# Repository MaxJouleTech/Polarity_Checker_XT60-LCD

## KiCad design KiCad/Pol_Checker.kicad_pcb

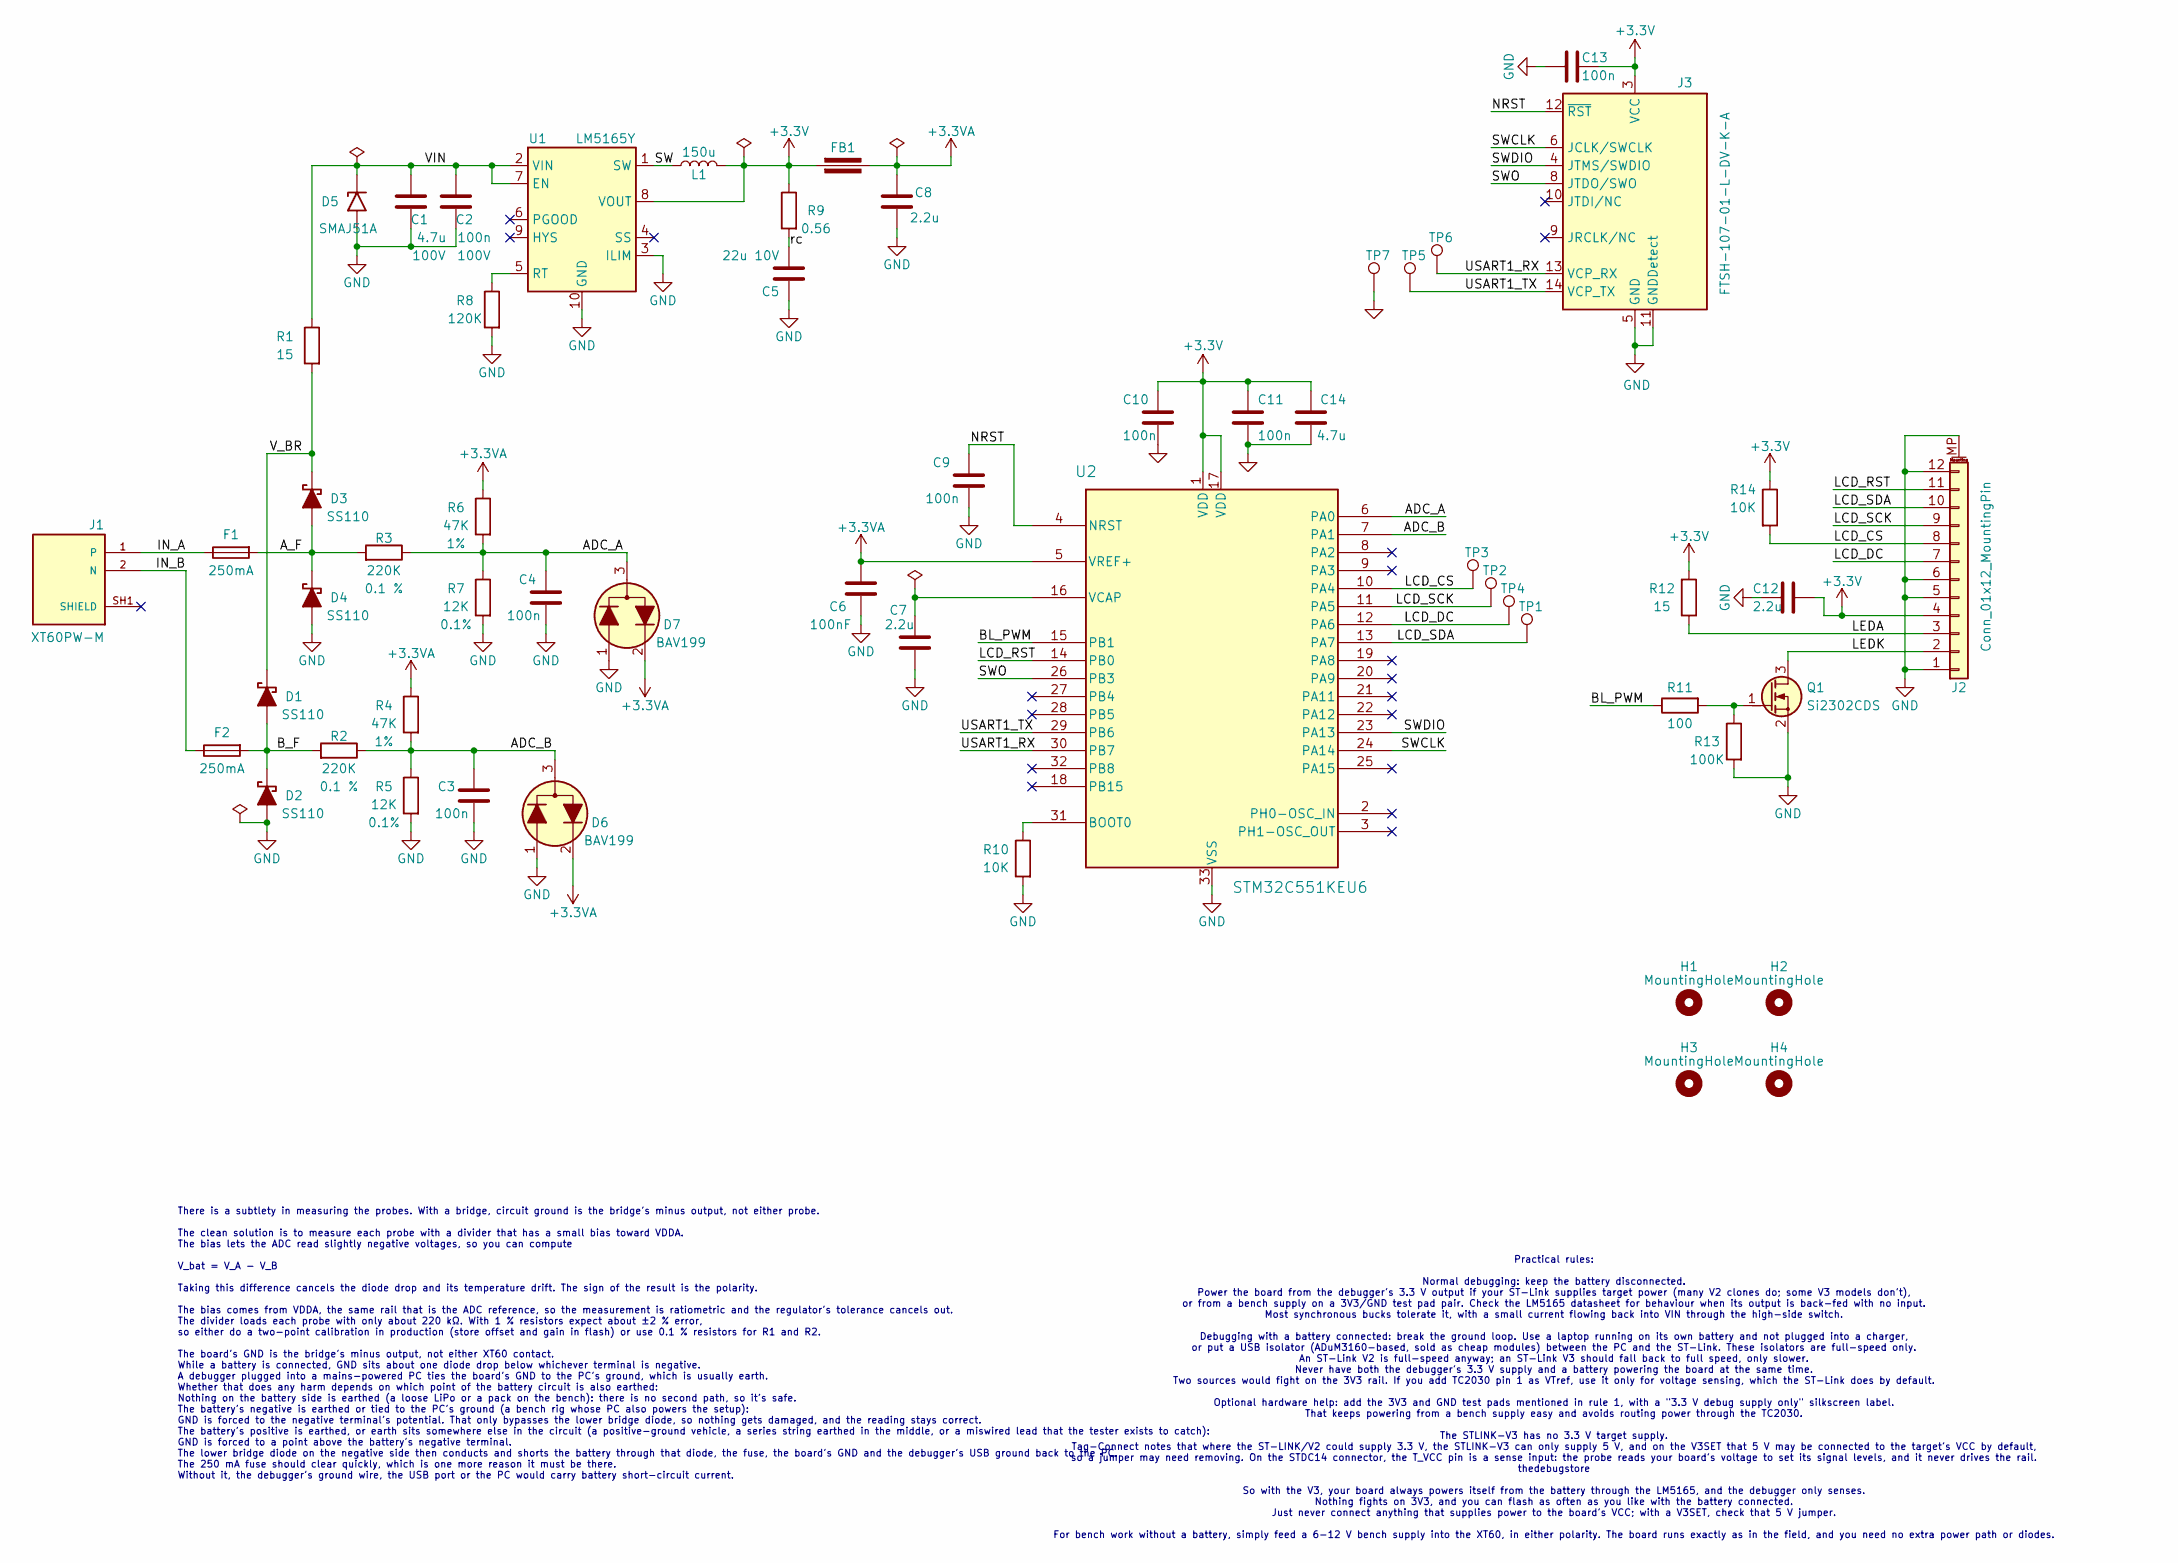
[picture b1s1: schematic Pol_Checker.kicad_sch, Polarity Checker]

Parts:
C1: 4.7u; C_1206_3216Metric; Tolerance 100V; MPN GRJ31CZ72A475ME01L
C2: 100n; C_0805_2012Metric; Tolerance 100V; MPN CL21B104KCFWPJF
C3, C4, C9, C10, C11, C13: 100n; C_0603_1608Metric; Tolerance 50V; MPN CL10B104KB8WPNC
C5: 22u 10V; C_1206_3216Metric; Tolerance 10V; MPN CL31B226KPHNNNE
C6: 100nF; C_0805_2012Metric; Tolerance 50V; MPN CL21B104KBCNFNC
C7, C8, C12: 2.2u; C_0805_2012Metric; Tolerance 25V; MPN CL21B225KAFNNNE
C14: 4.7u; C_0805_2012Metric; Tolerance 16V; MPN CL21A475KOFNNNG
D1, D2, D3, D4: SS110; D_SMA; MPN SS110LS
D5: SMAJ51A; D_SMA; MPN SMAJ51A-13-F
D6, D7: BAV199; SOT-23; MPN BAV199LT1G
F1, F2: 250mA; Fuse_1206_3216Metric; MPN 0466.250NR
FB1: Ferrite_Bead; L_0805_2012Metric; MPN BLM21PG221SN1D
H1, H2, H3, H4: MountingHole; MountingHole_2.2mm_M2
J1: XT60PW-M; AMASS_XT60PW-M; PARTREV 1.2
J2: Conn_01x12_MountingPin; Hirose_FH12-12S-0.5SH_1x12-1MP_P0.50mm_Horizontal; MPN FH12-12S-0.5SH(55)
J3: FTSH-107-01-L-DV-K-A; PinHeader_2x07_P1.27mm_Vertical_SMD; MPN FTSH-107-01-L-DV-K-A
L1: 150u; L_Coilcraft_LPS5030; MPN LPS5030-154MR
Q1: Si2302CDS; SOT-23; MPN SI2302CDS-T1-E3
R1: 15; R_1206_3216Metric; Tolerance 1%; MPN RC0603FR-0715RL
R2, R3: 220K; R_0805_2012Metric; Tolerance 0.1 %; MPN RP0603BRD07220KL
R4, R6: 47K; R_0603_1608Metric; Tolerance 1%; MPN RC0603FR-0747KL
R5, R7: 12K; R_0603_1608Metric; Tolerance 0.1%; MPN RT0603BRE0712KL
R8: 120K; R_0603_1608Metric; Tolerance 1%; MPN RC0603FR-10120KL
R9: 0.56; R_0603_1608Metric; Tolerance 1%; MPN RL0603FR-070R56L
R10, R14: 10K; R_0603_1608Metric; Tolerance 1%; MPN RC0603FR-0710KL
R11: 100; R_0603_1608Metric; Tolerance 1%; MPN RC0603FR-07100RL
R12: 15; R_0603_1608Metric; Tolerance 1%; MPN RC0603FR-0715RL
R13: 100K; R_0603_1608Metric; Tolerance 1%; MPN RC0603FR-07100KL
TP1, TP2, TP3, TP4, TP5, TP6: TestPoint; TestPoint_Pad_D1.5mm
TP7: TestPoint; TestPoint_Pad_2.0x2.0mm
U1: LM5165Y; Texas_S-PVSON-N10_ThermalVias; MPN LM5165YDRCR
U2: STM32C551KEU6; QFN-32-1EP_5x5mm_P0.5mm_EP3.1x3.1mm_ThermalVias; MPN STM32C551KEU6

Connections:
+3.3V: C10.2, C11.2, C12.1, C13.1, C14.1, FB1.1, J2.4, J3.3 (VCC), L1.2, R9.1, R12.2, R14.1, U1.8 (VOUT), U2.1 (VDD), U2.17 (VDD)
+3.3VA: C6.1, C8.1, D6.2 (K), D7.2 (K), FB1.2, R4.1, R6.1, U2.5 (VREF+)
/ADC_A: C4.1, D7.3 (C), R3.1, R6.2, R7.1, U2.6 (PA0)
/ADC_B: C3.1, D6.3 (C), R2.1, R4.2, R5.1, U2.7 (PA1)
/A_F: D3.2 (A), D4.1 (K), F1.2, R3.2
/BL_PWM: R11.1, U2.15 (PB1)
/B_F: D1.2 (A), D2.1 (K), F2.2, R2.2
/IN_A: F1.1, J1.1
/IN_B: F2.1, J1.2 (N)
/LCD_CS: J2.8, R14.2, TP3.1 (1_1), U2.10 (PA4)
/LCD_DC: J2.7, TP4.1 (1_1), U2.12 (PA6)
/LCD_RST: J2.11, U2.14 (PB0)
/LCD_SCK: J2.9, TP2.1 (1_1), U2.11 (PA5)
/LCD_SDA: J2.10, TP1.1 (1_1), U2.13 (PA7)
/LEDA: J2.3, R12.1
/LEDK: J2.2, Q1.3 (D)
/NRST: C9.1, J3.12 (~RST), U2.4 (NRST)
/SW: L1.1, U1.1 (SW)
/SWCLK: J3.6 (JCLK/SWCLK), U2.24 (PA14)
/SWDIO: J3.4 (JTMS/SWDIO), U2.23 (PA13)
/SWO: J3.8 (JTDO/SWO), U2.26 (PB3)
/USART1_RX: J3.13 (VCP_RX), TP6.1 (1_1), U2.30 (PB7)
/USART1_TX: J3.14 (VCP_TX), TP5.1 (1_1), U2.29 (PB6)
/VIN: C1.1, C2.1, D5.1 (A1), R1.1, U1.2 (VIN), U1.7 (EN)
/V_BR: D1.1 (K), D3.1 (K), R1.2
/rc: C5.1, R9.2
GND: C1.2, C2.2, C3.2, C4.2, C5.2, C6.2, C7.2, C8.2, C9.2, C10.1, C11.1, C12.2, C13.2, C14.2, D2.2 (A), D4.2 (A), D5.2 (A2), D6.1 (A), D7.1 (A), J2.1, J2.5, J2.6, J2.12, J2.MP (MountPin), J3.5 (GND), J3.7 (GND), J3.11 (GNDDetect), Q1.2 (S), R5.2, R7.2, R8.2, R10.2, R13.2, TP7.1 (1_1), U1.3 (ILIM), U1.10 (GND), U1.11 (GND), U2.33 (VSS)
unnamed: Q1.1 (G), R11.2, R13.1
unnamed: R8.1, U1.5 (RT)
unnamed: R10.1, U2.31 (BOOT0)
unnamed: C7.1, U2.16 (VCAP)

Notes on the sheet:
Practical rules: Normal debugging: keep the battery disconnected. Power the board from the debugger's 3.3 V output if your ST-Link supplies target power (many V2 clones do; some V3 models don't), or from a bench supply on a 3V3/GND test pad pair. Check the LM5165 datasheet for behaviour when its ou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
There is a subtlety in measuring the probes. With a bridge, circuit ground is the bridge's minus output, not either probe. The clean solution is to measure each probe with a divider that has a small bias toward VDDA. The bias lets the ADC read slightly negative voltages, so you can compute V_bat = 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

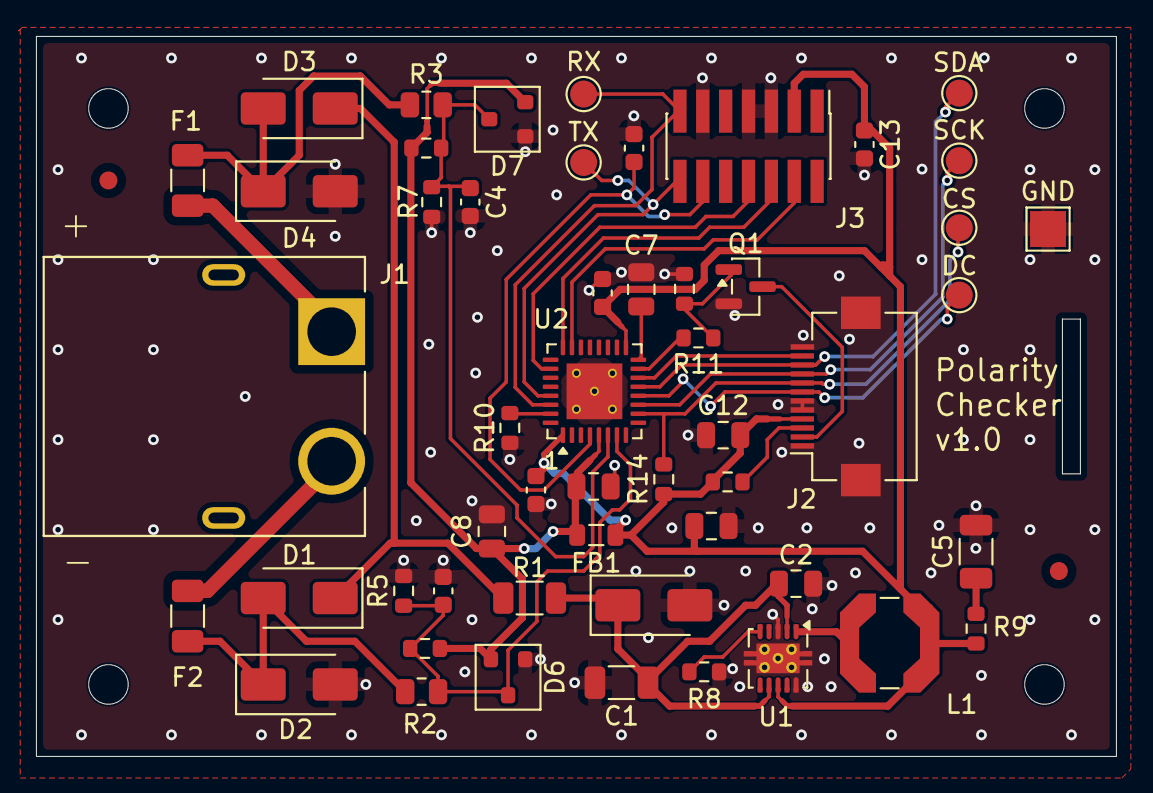
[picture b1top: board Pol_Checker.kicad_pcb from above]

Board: 2 copper layers, 60.0 x 40.0 mm, 58 parts (0 on the bottom side), 31 nets.

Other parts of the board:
FID1, FID2: Fiducial_1mm_Mask2mm
